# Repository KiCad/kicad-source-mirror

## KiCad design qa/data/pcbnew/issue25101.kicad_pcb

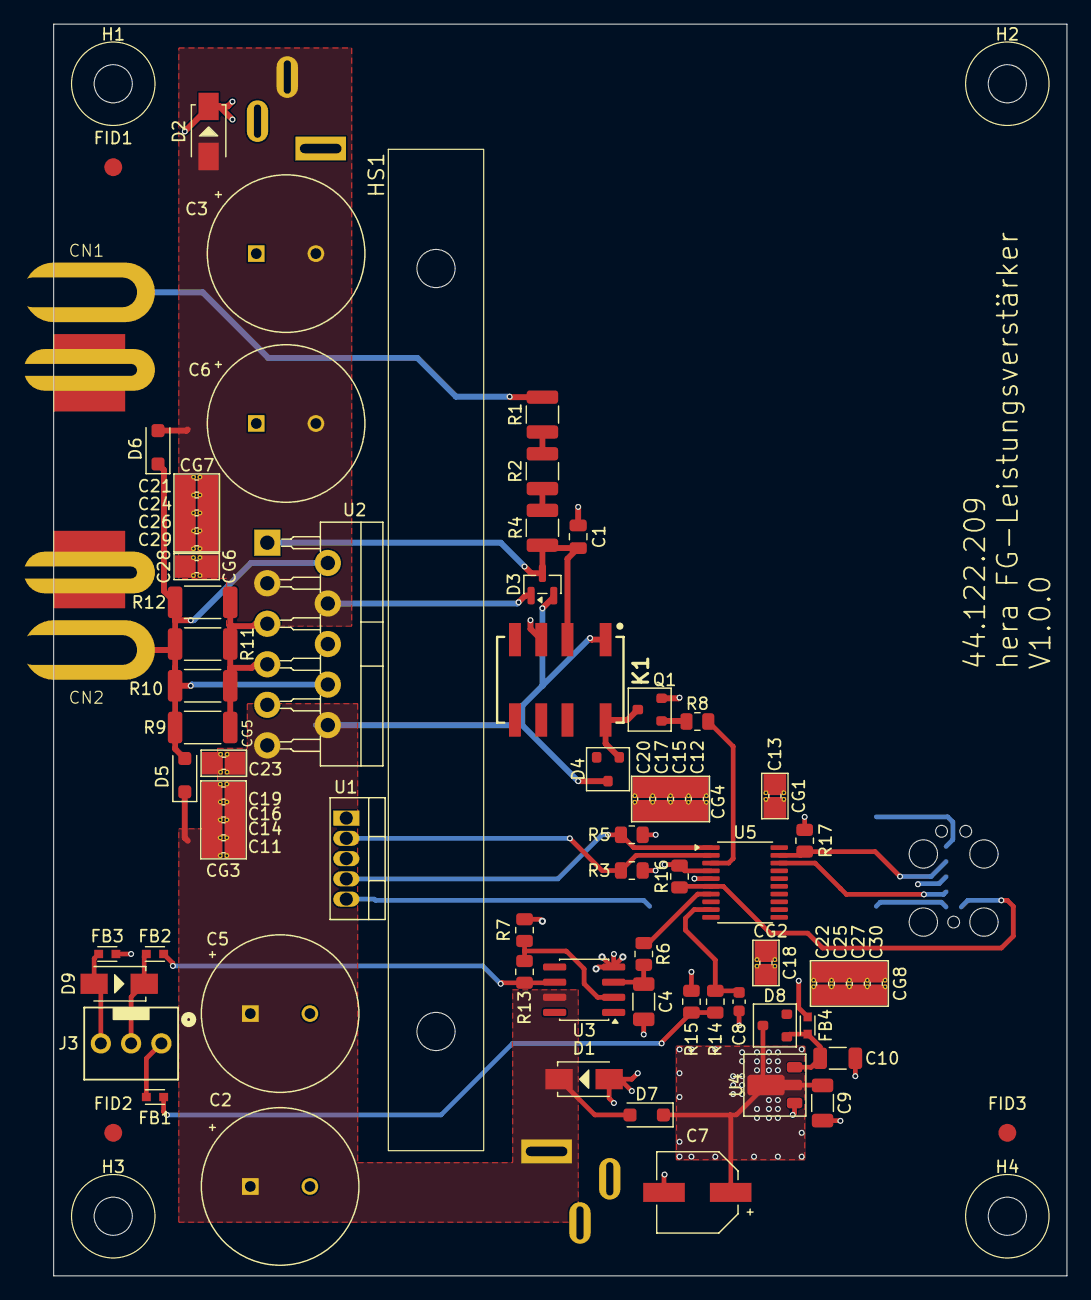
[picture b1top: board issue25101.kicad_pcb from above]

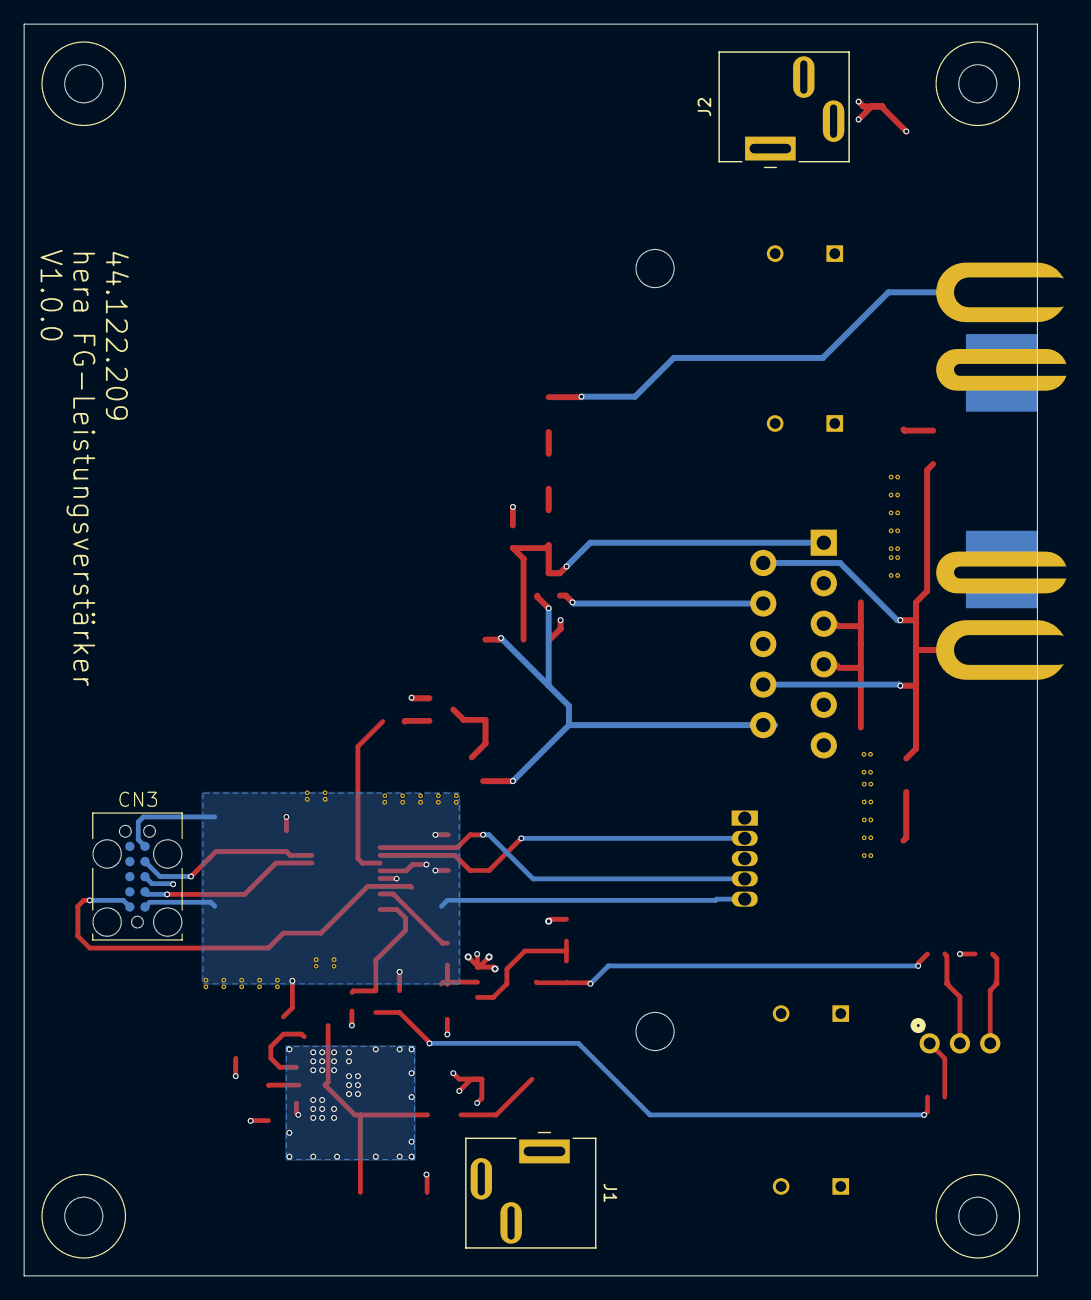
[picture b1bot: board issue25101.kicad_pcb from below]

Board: 4 copper layers, 85.0 x 105.0 mm, 89 parts (3 on the bottom side), 29 nets.

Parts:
C1: C; C_0805_2012Metric
C2, C3, C5, C6: 1mF; CP_Wurth_WCAP-ATLI-P5D13L25
C4: 10µ; C_1206_3216Metric
C7: 100µF; CP_Wurth_WCAP-ASLI-D6.3L7.7
C8: 100n; C_0603_1608Metric
C9, C10: 1µ; C_1206_3216Metric
C11, C12, C13, C18, C21, C22, C23, C28: 330n; C_0603_1608Metric
C14, C15, C24, C25: 47n; C_0603_1608Metric
C16, C17, C26, C27: 10n; C_0603_1608Metric
C19, C20, C29, C30: 1n; C_0603_1608Metric
CG1, CG2, CG5, CG6: C-Group_1x_0603
CG3, CG4, CG7, CG8: C-Group_4x_0603
CN1: 5-1634523-1; BNC_Steckverbinder_geloetet_gedreht
CN2: 5-1634523-1; BNC_Steckverbinder_geloetet
CN3: TC2050; TC2050-IDC
D1, D2, D9: SMAJ24A; D_Wurth_WE-TVSP-DO214-AC-400W_UNI
D3: BAT54S; SOT-23
D4, D8: BAS16; SOT-23
D5, D6, D7: SM5819PL-TP; D_SOD-123F
FB1, FB2, FB3, FB4: 74279266; FB_Wurth_WE-CBF-0603_W2.2
FID1, FID2, FID3: Fiducial; Fiducial_1.5mm_Mask3mm
H1, H2, H3, H4: MountingHole; MountingHole_3.2mm_M3
HS1: SK_96_84_SA; SK_96_84
J1, J2: 694106402002; J_Wurth_WR-DC_694106402002
J3: 0022272031
K1: AGQ200A24Z; AGQ200_Type_A_Surface_Mount
Q1: BC817-40-AQ; SOT-23
R1, R2, R4: 1k; R_1210_3225Metric
R3, R5, R16, R17: 10k; R_0805_2012Metric
R6: 2k2; R_0805_2012Metric
R7: 13k; R_0805_2012Metric
R8, R15: 1k; R_0805_2012Metric
R9, R10: 2R; R_2010_5025Metric
R11, R12: 2R2; R_2010_5025Metric
R13: 91k; R_0805_2012Metric
R14: 10R; R_0805_2012Metric
U1: TC74A0-3.3VAT; TO-220-5_Vertical
U2: OPA541AP; TO-220-11_P3.4x5.08mm_StaggerOdd_Lead4.85mm_Vertical
U3: OPA1655D; SOIC-8_3.9x4.9mm_P1.27mm
U4: AP7383-33Y; SOT-89-3
U5: STM32C011F6Px; TSSOP-20_4.4x6.5mm_P0.65mm

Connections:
+3V3: C12.1, C13.1, C15.1, C17.1, C18.1, C20.1, C22.1, C25.1, C27.1, C30.1, CG1.+, CG1.+1 (+), CG1.+2 (+), CG2.+, CG2.+1 (+), CG2.+2 (+), CG4.+, CG4.+1 (+), CG4.+2 (+), CG4.+3 (+), CG4.+4 (+), CG4.+5 (+), CG8.+, CG8.+1 (+), CG8.+2 (+), CG8.+3 (+), CG8.+4 (+), CG8.+5 (+), CN3.1 (VCC), CN3.5 (GND_+5V), FB4.2, R3.1, R5.1, R15.1, R16.1, U1.5 (VDD), U5.4 (VDD)
+24V: C2.1, C5.1, C11.1, C14.1, C16.1, C19.1, C23.1, CG3.+, CG3.+1 (+), CG3.+2 (+), CG3.+3 (+), CG3.+4 (+), CG3.+5 (+), CG5.+, CG5.+1 (+), CG5.+2 (+), D1.1 (Cathode), D3.2 (K), D4.3 (K), D5.1 (K), D7.2 (A), J1.1, K1.1 (+), U2.10 (V+), U2.11 (V+), U3.7 (V+)
-24V: C3.2, C6.2, C21.1, C24.1, C26.1, C28.1, C29.1, CG6.+, CG6.+1 (+), CG6.+2 (+), CG7.+, CG7.+1 (+), CG7.+2 (+), CG7.+3 (+), CG7.+4 (+), CG7.+5 (+), D2.2 (Anode), D3.1 (A), D6.2 (A), J2.3, U2.3 (V-), U2.4 (V-)
/24V_gepuffert: C7.1, C9.1, D7.1 (K), D8.3 (K), U4.2 (IN)
/DEBUG_SWCLK: CN3.4 (TCK_SWCLK), R17.1, U5.19 (DEBUG_SWCLK)
/DEBUG_SWDIO: CN3.2 (JTMS_SWDIO), U5.18 (DEBUG_SWDIO)
/FAN_PWM_µC: R6.1, U5.7 (TIM1_CH1)
/FAN_SENSE_µC: C8.1, R14.2, U5.9 (TIM3_ETR)
/OUTPUT_ON: R8.1, U5.3 (PC15)
/RESET: CN3.10 (RESET), R16.2, U5.6 (PF2)
/SCL: R5.2, U1.4 (SCLK), U5.1 (I2C1_SCL)
/SDA: R3.2, U1.2 (SDA), U5.2 (I2C1_SDA)
GND: C1.2, C2.2, C3.1, C4.2, C5.2, C6.1, C7.2, C8.2, C9.2, C10.2, C11.2, C12.2, C13.2, C14.2, C15.2, C16.2, C17.2, C18.2, C19.2, C20.2, C21.2, C22.2, C23.2, C24.2, C25.2, C26.2, C27.2, C28.2, C29.2, C30.2, CG1.-, CG1.-1 (-), CG1.-2 (-), CG2.-, CG2.-1 (-), CG2.-2 (-), CG3.-, CG3.-1 (-), CG3.-2 (-), CG3.-3 (-), CG3.-4 (-), CG3.-5 (-), CG4.-, CG4.-1 (-), CG4.-2 (-), CG4.-3 (-), CG4.-4 (-), CG4.-5 (-), CG5.-, CG5.-1 (-), CG5.-2 (-), CG6.-, CG6.-1 (-), CG6.-2 (-), CG7.-, CG7.-1 (-), CG7.-2 (-), CG7.-3 (-), CG7.-4 (-), CG7.-5 (-), CG8.-, CG8.-1 (-), CG8.-2 (-), CG8.-3 (-), CG8.-4 (-), CG8.-5 (-), CN1.2 (Ext), CN2.2 (Ext), CN3.3 (GND), D1.2 (Anode), D2.1 (Cathode), FB3.1, J1.3, J2.1, K1.3, Q1.2 (E), R7.1, R17.2, U1.3 (GND), U3.4 (V-), U4.1, U5.5 (VSS)
unnamed: CN1.1 (In), R1.2
unnamed: CN2.1 (In), D5.2 (A), D6.1 (K), R9.2, R10.2, R11.2, R12.2, U2.2 (-), U2.8 (CS)
unnamed: C1.1, D3.3 (COM), K1.2, R4.1, U2.1 (+)
unnamed: D4.1 (A), K1.8 (-), Q1.3 (C)
unnamed: C10.1, D8.1 (A), FB4.1, U4.3 (OUT)
unnamed: D9.2 (Anode), FB3.2, J3.3
unnamed: D9.1 (Cathode), FB2.2, J3.2
unnamed: FB1.1, R14.1, R15.2
unnamed: FB1.2, J3.1
unnamed: FB2.1, R13.2, U3.6
unnamed: Q1.1 (B), R8.2
unnamed: R1.1, R2.2
unnamed: R2.1, R4.2
unnamed: R9.1, R10.1, R11.1, R12.1, U2.5, U2.7
unnamed: C4.1, R6.2, U3.3 (+)
unnamed: R7.2, R13.1, U3.2 (-)

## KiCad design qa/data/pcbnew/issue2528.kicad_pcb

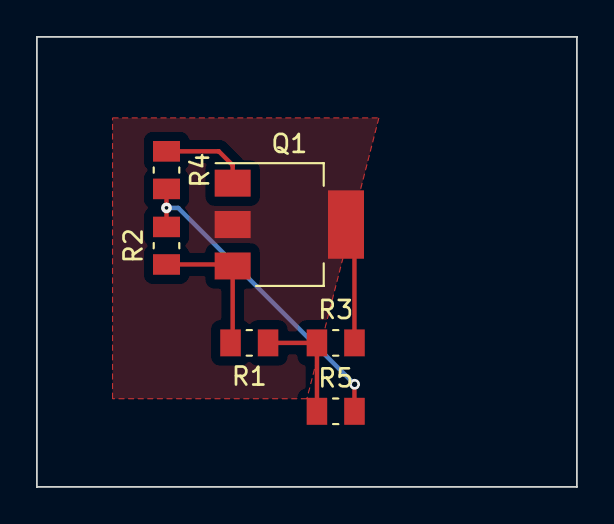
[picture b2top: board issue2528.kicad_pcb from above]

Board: 2 copper layers, 30.0 x 25.0 mm, 6 parts (0 on the bottom side), 5 nets.

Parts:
Q1: Q_NPN_Darlington_ECBC; SOT-223
R1, R5: 10k; R_0805_2012Metric_Pad1.15x1.50mm_HandSolder
R2: 1k; R_0805_2012Metric_Pad1.15x1.50mm_HandSolder
R3: 100R; R_0805_2012Metric_Pad1.15x1.50mm_HandSolder
R4: 10R; R_0805_2012Metric_Pad1.15x1.50mm_HandSolder

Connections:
/Base: Q1.3, R1.2, R2.1
/Col: Q1.2, Q1.4, R3.2
unnamed: Q1.1, R4.1
unnamed: R1.1, R3.1, R5.1
unnamed: R2.2, R4.2, R5.2
